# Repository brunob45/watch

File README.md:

# Main program for "analogic" numeric watch

 Code will work with my own design, available :
 https://oshpark.com/shared_projects/29Yy2Qri

 Microcontroller is an Atmel ATTiny88.
 http://www.atmel.com/images/doc8008.pdf
 
 Idea inspired from : 
 http://spikenzielabs.com/SpikenzieLabs/SolderTime.html

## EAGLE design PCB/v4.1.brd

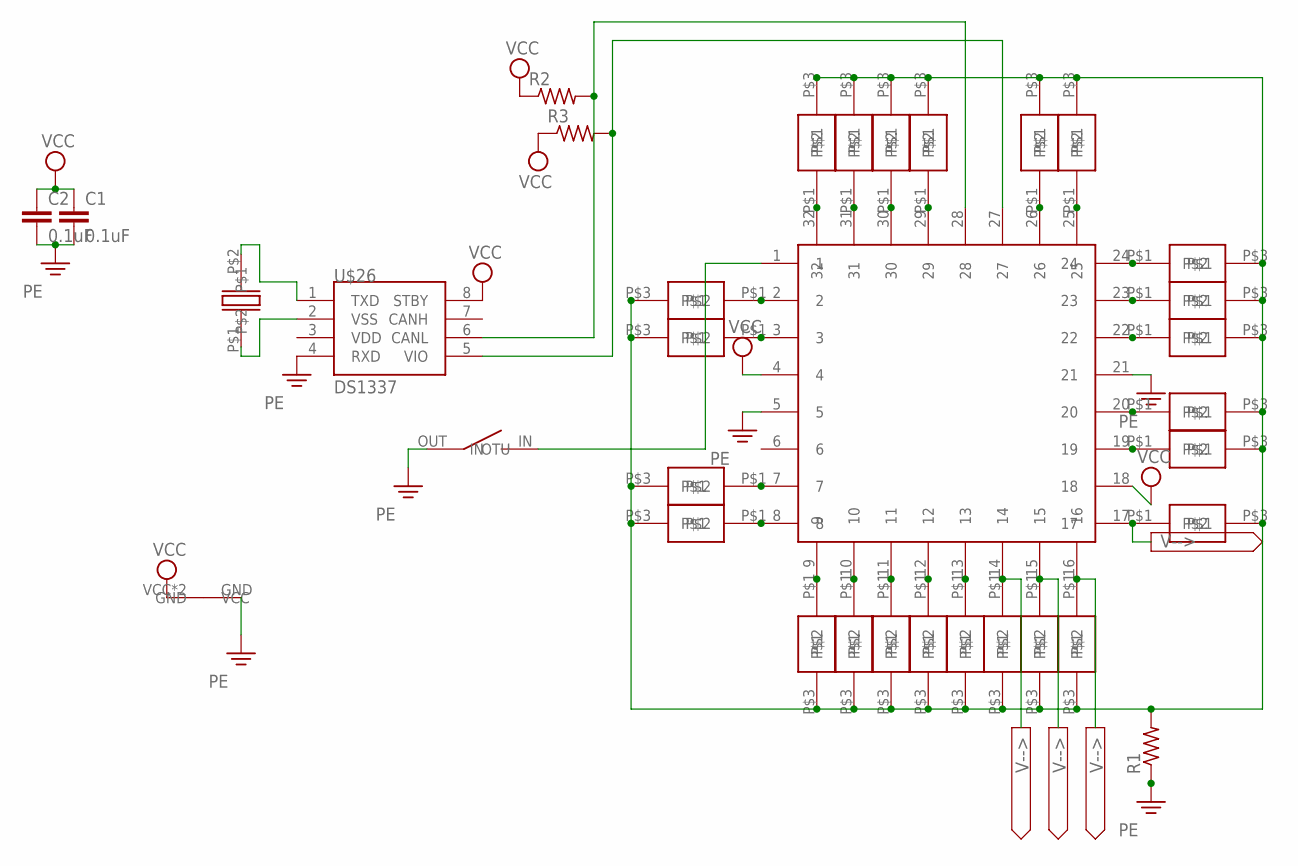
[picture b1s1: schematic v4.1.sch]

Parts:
C1, C2: 0.1uF; C0805K
R1, R2, R3: R-US_R0805; R0805
U$1, U$2, U$3, U$4, U$5, U$6, U$7, U$8, U$9, U$10, U$11, U$12, U$13, U$14, U$15, U$16, U$17, U$18, U$19, U$20, U$21, U$22, U$23, U$24: SMDLED
U$25: ATTINY88; 32-TQFT
U$26: DS1337; 8-SOIC
U$27: BAT2009
U$28: INT2
U$29: SMDCRYSTAL

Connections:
unnamed: U$16.P$1, U$25.2
unnamed: U$17.P$1, U$25.3
unnamed: U$7.P$1, U$25.7
unnamed: U$8.P$1, U$25.8
unnamed: U$18.P$1, U$25.9
unnamed: U$19.P$1, U$25.10
unnamed: U$20.P$1, U$25.11
unnamed: U$1.P$1, U$25.12
unnamed: U$2.P$1, U$25.13
unnamed: U$3.P$1, U$25.14
unnamed: U$11.P$1, U$25.17
unnamed: U$24.P$1, U$25.26
unnamed: U$9.P$1, U$25.25
unnamed: U$6.P$1, U$25.24
unnamed: U$22.P$1, U$25.23
unnamed: U$21.P$1, U$25.22
unnamed: U$25.1, U$28.IN
unnamed: U$10.P$1, U$25.20
unnamed: U$23.P$1, U$25.29
unnamed: U$13.P$1, U$25.30
unnamed: U$14.P$1, U$25.31
unnamed: U$15.P$1, U$25.32
unnamed: R1.2, U$1.P$3, U$2.P$3, U$3.P$3, U$4.P$3, U$5.P$3, U$6.P$3, U$7.P$3, U$8.P$3, U$9.P$3, U$10.P$3, U$11.P$3, U$12.P$3, U$13.P$3, U$14.P$3, U$15.P$3, U$16.P$3, U$17.P$3, U$18.P$3, U$19.P$3, U$20.P$3, U$21.P$3, U$22.P$3, U$23.P$3, U$24.P$3
unnamed: U$12.P$1, U$25.19
unnamed: U$26.2 (VSS), U$29.P$1
unnamed: U$26.1 (TXD), U$29.P$2
unnamed: U$5.P$1, U$25.16
unnamed: U$4.P$1, U$25.15
PE: C1.2, C2.2, R1.1, U$25.5, U$25.21, U$26.4 (RXD), U$27.GND, U$28.OUT (OTU)
SCL: R2.2, U$25.28, U$26.6 (CANL)
SDA: R3.2, U$25.27, U$26.5 (VIO)
VCC: C1.1, C2.1, R2.1, R3.1, U$25.4, U$25.18, U$26.8 (STBY), U$27.VCC, U$27.VCC2 (VCC)

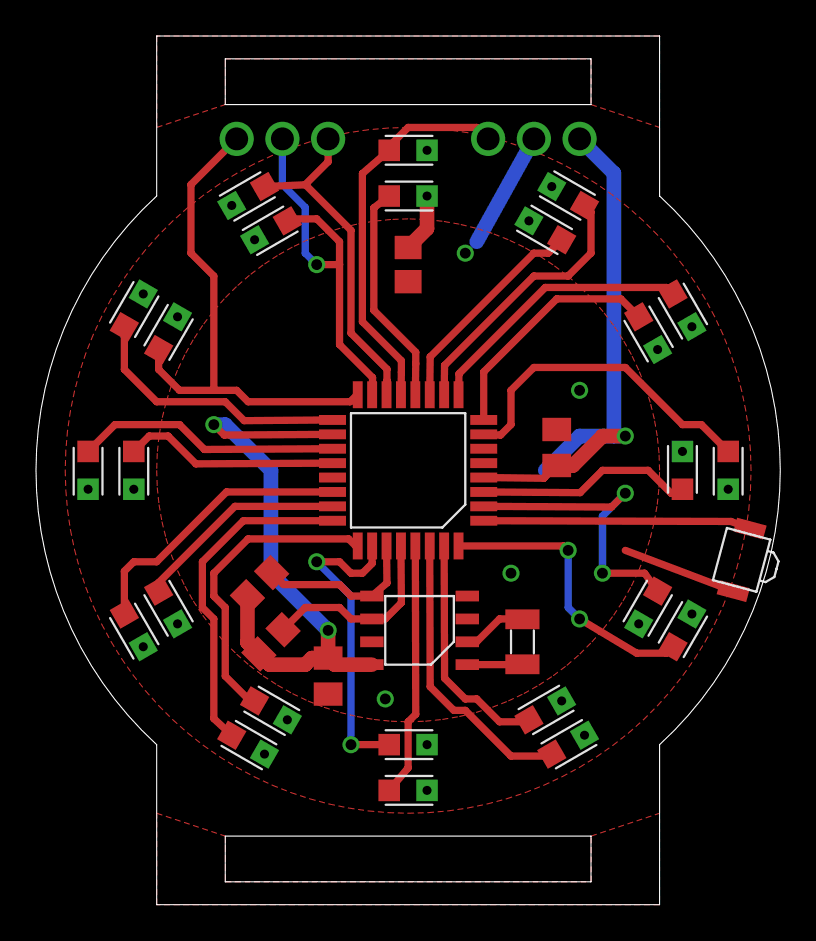
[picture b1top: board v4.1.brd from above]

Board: 2 copper layers, 41.3 x 48.3 mm, 34 parts (1 on the bottom side), 32 nets.

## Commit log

2016-12-20 Add documentation
2016-12-20 add timer1 namespace and functions
2016-12-20 add timer0 namespace and functions
2016-12-20 add timer namespaces and functions -- make them classes?
2016-12-20 bug correction, add interrupt handler in Button, pin direction in LED, remove interrupt disable from interrupt handler
2016-12-20 Set theme jekyll-theme-tactile
2016-12-20 Set theme jekyll-theme-time-machine
2016-12-21 move src files to src directory
2016-12-21 add header "util.h"
2016-12-21 replace timer namespaces by static classes fix makefile
2016-12-21 make display, twi and rtc classes
2016-12-22 make button a class
2017-01-13 make local global variables static
2017-01-17 make static variables "externs" and update headers
2017-01-18 temporarily make the program do nothing
2017-01-18 update Makefile to support fuse programmation
2017-01-19 add method for delay in ms for timers
2017-01-19 main now contains a test for the 12:00 led
2017-01-23 Add PCB files to git
2017-02-14 Button making LEDs flashing and increment
2017-02-14 Watch enters sleep mode when left untouched for 5 seconds
2017-02-22 Now using state enum
2017-02-23 Fix setTime and clean code
2017-02-23 Remove extern variable declaration from headers
2017-02-23 Time is now saved in RTC
2017-02-24 Added speedup for setting time
2017-02-24 added functions proto in main.h
2017-04-26 final PCB sketch and fix time setting bug
2017-04-26 Display : rename LED arrays
2017-04-26 RTC time bug : data is now stored in BCD
2017-04-26 fix comment
2017-04-26 remove commented code
2017-04-26 added alias to set which LED ring is minutes and hours
2017-04-26 BCD : remove redundant lines
2017-05-29 Using avr/power.h for power management
2017-06-14 Remove interrupts and apply state pattern
2017-06-15 rename src folder to code, as it is used at another location
2017-06-15 change RTC and TWI classes to namespaces
2017-06-15 include vscode settings files
2017-06-15 insert static code in TWI header
2017-06-15 cleanup display showTime function
2017-06-15 repo cleaning : remove unused files
2017-06-15 Remove states from main and convert display to namespace
2017-06-15 Remove redundant #include
2017-06-15 Fix undefined macro
2017-06-15 change current display array to struct
2017-06-15 fix bitvalue mask mistake
2017-06-15 add init and shutDown functions to Display
2017-06-15 change tick static flag to a GPIOR flag (much faster)
2017-06-16 add shortcuts for linux
2017-06-16 resolve merge conflicts
2017-06-16 add timer0 initialization
2017-06-16 Fix button state not updating each tick
2017-06-16 add int1 interrupt handling
2017-06-16 change button state flags to GPIOR and remove sleep_cnt
2017-06-16 add pinout definition file
2017-06-16 insure button state at startup
2017-06-16 fix display init values and remove redundant code
2017-06-16 fix button state on startup
2017-06-16 fix button enable interrupt location
2017-06-17 add fuses definition to main
2017-06-17 fix button state reading problem
2017-06-17 fix display state not updating to sleep after timeout
2017-06-17 showing is now gpior, DDRx fix and pgm_read fix
2017-06-17 fix time setting details
2017-06-17 Refactoring and power saving (#4)
    * Remove interrupts and apply state pattern
    * rename src folder to code, as it is used at another location
    * change RTC and TWI classes to namespaces
    * include vscode settings files
    * insert static code in TWI header
    * cleanup display showTime function
2017-06-18 Tune timer to reflect real time better
